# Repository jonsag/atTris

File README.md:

# atTris

## tinyTris

Adapted from work by jaromaz at [https://github.com/jaromaz/ATtiny-Tetris-Gold](https://github.com/jaromaz/ATtiny-Tetris-Gold).  

### Hardware

AS programmer I use [this one](https://github.com/jonsag/ardAVRProgrammer)  

### Software

Connect the avrProgrammer  
Insert the MCU  

Upload the hex  

>$ avrdude -c avrisp -b 19200 -p t85 -P /dev/ttyUSB0 -v -U flash:w:ATtiny-Tetris-Gold.ino.tiny8.hex:i

Set fuses  

>$ avrdude -c avrisp -b 19200 -p t85 -P /dev/ttyUSB0 -v -U lfuse:w:0xf1:m -U hfuse:w:0xdf:m -U efuse:w:0xff:m

## megaTris

My adaption of robsoncuoto's project at [https://github.com/robsoncouto/gm328a_rev_eng](https://github.com/robsoncouto/gm328a_rev_eng).  

## Notes

Reading of ATtiny85, no1, with Tetris  

    Atmega chip detector.
    Written by Nick Gammon.
    Version 1.20
    Compiled on Feb 15 2021 at 16:17:48 with Arduino IDE 10813.
    Attempting to enter ICSP programming mode ...
    Entered programming mode OK.
    Signature = 0x1E 0x93 0x0B 
    Processor = ATtiny85
    Flash memory size = 8192 bytes.
    LFuse = 0x62 
    HFuse = 0xDF 
    EFuse = 0xFF 
    Lock byte = 0xFF 
    Clock calibration = 0x91 
    No bootloader support.

    First 256 bytes of program memory:

    00: 0x4F 0xC2 0x26 0xC5 0x27 0xC9 0x67 0xC2 0x66 0xC2 0x7E 0xCA 0x64 0xC2 0x63 0xC2 
    10: 0x62 0xC2 0x61 0xC2 0x60 0xC2 0x5F 0xC2 0x5E 0xC2 0x5D 0xC2 0x5C 0xC2 0x77 0x77 
    20: 0x00 0x00 0x70 0x77 0x70 0x00 0x70 0x00 0x70 0x77 0x70 0x07 0x70 0x07 0x70 0x07 
    30: 0x00 0xEE 0x70 0x77 0x00 0x0E 0x70 0x07 0xEE 0x00 0x00 0x00 0x00 0x00 0x00 0x00 
    40: 0x00 0x00 0x00 0x00 0x00 0x3F 0x00 0x00 0x00 0x00 0x00 0x00 0x00 0x00 0x00 0x0C 
    50: 0x0C 0x00 0x60 0x30 0x18 0x0C 0x06 0x03 0x01 0x00 0x3E 0x63 0x73 0x7B 0x6F 0x67 
    60: 0x3E 0x00 0x0C 0x0E 0x0C 0x0C 0x0C 0x0C 0x3F 0x00 0x1E 0x33 0x30 0x1C 0x06 0x33 
    70: 0x3F 0x00 0x1E 0x33 0x30 0x1C 0x30 0x33 0x1E 0x00 0x38 0x3C 0x36 0x33 0x7F 0x30 
    80: 0x78 0x00 0x3F 0x03 0x1F 0x30 0x30 0x33 0x1E 0x00 0x1C 0x06 0x03 0x1F 0x33 0x33 
    90: 0x1E 0x00 0x3F 0x33 0x30 0x18 0x0C 0x0C 0x0C 0x00 0x1E 0x33 0x33 0x1E 0x33 0x33 
    A0: 0x1E 0x00 0x1E 0x33 0x33 0x3E 0x30 0x18 0x0E 0x00 0x0C 0x1E 0x33 0x33 0x3F 0x33 
    B0: 0x33 0x00 0x3F 0x66 0x66 0x3E 0x66 0x66 0x3F 0x00 0x3C 0x66 0x03 0x03 0x03 0x66 
    C0: 0x3C 0x00 0x1F 0x36 0x66 0x66 0x66 0x36 0x1F 0x00 0x7F 0x46 0x16 0x1E 0x16 0x46 
    D0: 0x7F 0x00 0x7F 0x46 0x16 0x1E 0x16 0x06 0x0F 0x00 0x3C 0x66 0x03 0x03 0x73 0x66 
    E0: 0x7C 0x00 0x33 0x33 0x33 0x3F 0x33 0x33 0x33 0x00 0x1E 0x0C 0x0C 0x0C 0x0C 0x0C 
    F0: 0x1E 0x00 0x78 0x30 0x30 0x30 0x33 0x33 0x1E 0x00 0x67 0x66 0x36 0x1E 0x36 0x66 

    Programming mode off.

Reading of ATtiny85, no2, with Tetris  

    Atmega chip detector.
    Written by Nick Gammon.
    Version 1.20
    Compiled on Feb 15 2021 at 16:17:48 with Arduino IDE 10813.
    Attempting to enter ICSP programming mode ...
    Entered programming mode OK.
    Signature = 0x1E 0x93 0x0B 
    Processor = ATtiny85
    Flash memory size = 8192 bytes.
    LFuse = 0xF1 
    HFuse = 0xDF 
    EFuse = 0xFF 
    Lock byte = 0xFF 
    Clock calibration = 0x86 
    No bootloader support.

    First 256 bytes of program memory:

    00: 0x4F 0xC2 0x26 0xC5 0x27 0xC9 0x67 0xC2 0x66 0xC2 0x7E 0xCA 0x64 0xC2 0x63 0xC2 
    10: 0x62 0xC2 0x61 0xC2 0x60 0xC2 0x5F 0xC2 0x5E 0xC2 0x5D 0xC2 0x5C 0xC2 0x77 0x77 
    20: 0x00 0x00 0x70 0x77 0x70 0x00 0x70 0x00 0x70 0x77 0x70 0x07 0x70 0x07 0x70 0x07 
    30: 0x00 0xEE 0x70 0x77 0x00 0x0E 0x70 0x07 0xEE 0x00 0x00 0x00 0x00 0x00 0x00 0x00 
    40: 0x00 0x00 0x00 0x00 0x00 0x3F 0x00 0x00 0x00 0x00 0x00 0x00 0x00 0x00 0x00 0x0C 
    50: 0x0C 0x00 0x60 0x30 0x18 0x0C 0x06 0x03 0x01 0x00 0x3E 0x63 0x73 0x7B 0x6F 0x67 
    60: 0x3E 0x00 0x0C 0x0E 0x0C 0x0C 0x0C 0x0C 0x3F 0x00 0x1E 0x33 0x30 0x1C 0x06 0x33 
    70: 0x3F 0x00 0x1E 0x33 0x30 0x1C 0x30 0x33 0x1E 0x00 0x38 0x3C 0x36 0x33 0x7F 0x30 
    80: 0x78 0x00 0x3F 0x03 0x1F 0x30 0x30 0x33 0x1E 0x00 0x1C 0x06 0x03 0x1F 0x33 0x33 
    90: 0x1E 0x00 0x3F 0x33 0x30 0x18 0x0C 0x0C 0x0C 0x00 0x1E 0x33 0x33 0x1E 0x33 0x33 
    A0: 0x1E 0x00 0x1E 0x33 0x33 0x3E 0x30 0x18 0x0E 0x00 0x0C 0x1E 0x33 0x33 0x3F 0x33 
    B0: 0x33 0x00 0x3F 0x66 0x66 0x3E 0x66 0x66 0x3F 0x00 0x3C 0x66 0x03 0x03 0x03 0x66 
    C0: 0x3C 0x00 0x1F 0x36 0x66 0x66 0x66 0x36 0x1F 0x00 0x7F 0x46 0x16 0x1E 0x16 0x46 
    D0: 0x7F 0x00 0x7F 0x46 0x16 0x1E 0x16 0x06 0x0F 0x00 0x3C 0x66 0x03 0x03 0x73 0x66 
    E0: 0x7C 0x00 0x33 0x33 0x33 0x3F 0x33 0x33 0x33 0x00 0x1E 0x0C 0x0C 0x0C 0x0C 0x0C 
    F0: 0x1E 0x00 0x78 0x30 0x30 0x30 0x33 0x33 0x1E 0x00 0x67 0x66 0x36 0x1E 0x36 0x66 

    Programming mode off.

## ATtinyArcade

[webbgoggles, AttinyArcade](https://github.com/webboggles/AttinyArcade)

## More games

[andyhighnumber, Attiny-Arduino-Games](https://github.com/andyhighnumber/Attiny-Arduino-Games)  
>>>>>>> 1e57dbd8131bc683bb3b376d9e93d66b33e94c2e

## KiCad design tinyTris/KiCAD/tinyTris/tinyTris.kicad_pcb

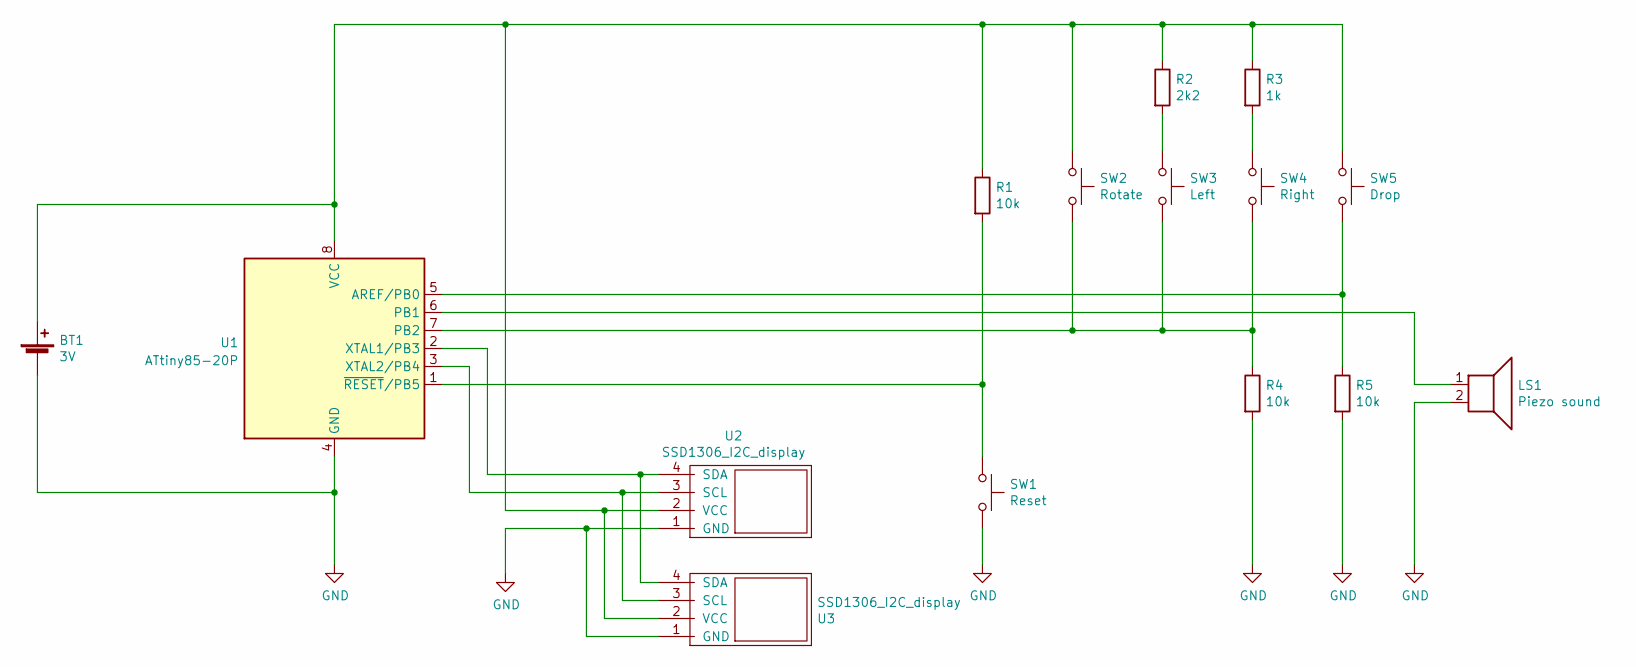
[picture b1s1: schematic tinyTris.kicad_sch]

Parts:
BT1: 3V; BatteryHolder_Keystone_103_1x20mm
LS1: Piezo sound; Buzzer_TDK_PS1240P02BT_D12.2mm_H6.5mm_large
R1, R4, R5: 10k; R_Axial_DIN0207_L6.3mm_D2.5mm_P10.16mm_Horizontal_larger_pa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
R2: 2k2; R_Axial_DIN0207_L6.3mm_D2.5mm_P10.16mm_Horizontal_larger_pa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
R3: 1k; R_Axial_DIN0207_L6.3mm_D2.5mm_P10.16mm_Horizontal_larger_pa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
SW1: Reset; SW_PUSH_6mm_large
SW2: Rotate; SW_PUSH_6mm_large
SW3: Left; SW_PUSH_6mm_large
SW4: Right; SW_PUSH_6mm_large
SW5: Drop; SW_PUSH_6mm_large
U1: ATtiny85-20P; DIP-8_W7.62mm_Socket_w_dip_packet_LongPads
U2: SSD1306_I2C_display; SSD1306_I2C_0.96_OLED_display_no_display_large
U3: SSD1306_I2C_display; SSD1306_I2C_0.96_OLED_display_large

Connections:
GND: BT1.2 (-), LS1.2, R4.2, R5.2, SW1.2, U1.4 (GND), U2.1 (GND), U3.1 (GND)
unnamed: BT1.1 (+), R1.1, R2.1, R3.1, SW2.1, SW5.1, U1.8 (VCC), U2.2 (VCC), U3.2 (VCC)
unnamed: LS1.1, U1.6 (PB1)
unnamed: R1.2, SW1.1, U1.1 (~RESET/PB5)
unnamed: R2.2, SW3.1
unnamed: R3.2, SW4.1
unnamed: R4.1, SW2.2, SW3.2, SW4.2, U1.7 (PB2)
unnamed: R5.1, SW5.2, U1.5 (AREF/PB0)
unnamed: U1.2 (XTAL1/PB3), U2.4 (SDA), U3.4 (SDA)
unnamed: U1.3 (XTAL2/PB4), U2.3 (SCL), U3.3 (SCL)

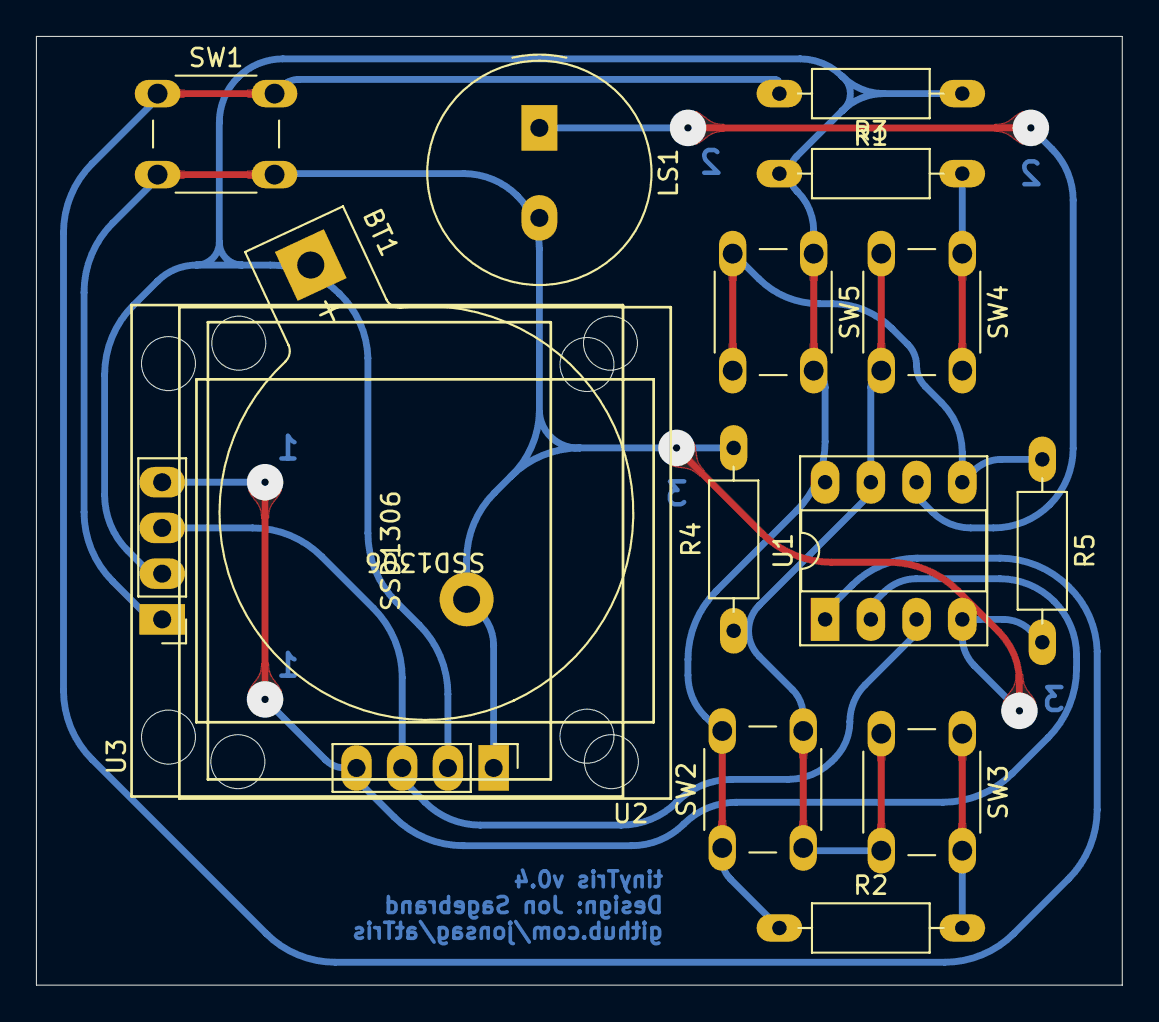
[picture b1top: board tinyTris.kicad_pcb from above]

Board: 2 copper layers, 60.3 x 52.7 mm, 15 parts (0 on the bottom side), 10 nets.

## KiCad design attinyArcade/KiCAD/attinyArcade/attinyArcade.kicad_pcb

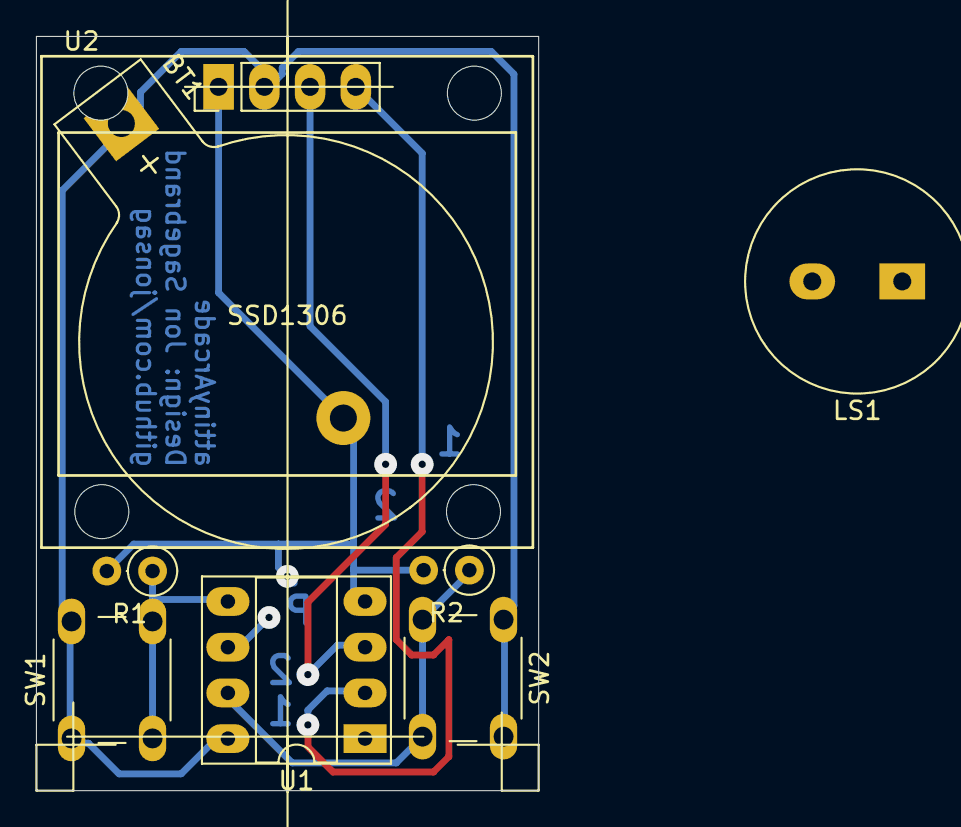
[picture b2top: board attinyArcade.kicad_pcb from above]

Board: 2 copper layers, 27.9 x 41.9 mm, 8 parts (0 on the bottom side), 7 nets.

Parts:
BT1: 3V; BatteryHolder_Keystone_103_1x20mm
LS1: Speaker; Buzzer_TDK_PS1240P02BT_D12.2mm_H6.5mm_large
R1, R2: 10k; R_Axial_DIN0207_L6.3mm_D2.5mm_P2.54mm_Vertical_large
SW1, SW2: SW_Push; SW_PUSH_6mm_large
U1: ATtiny85-20P; DIP-8_W7.62mm_Socket_w_dip_packet_LongPads
U2: SSD1306_I2C_display; SSD1306_I2C_0.96_OLED_display_large

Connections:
GND: BT1.2 (-), LS1.2, R1.2, R2.2, U1.4 (GND), U2.1 (GND)
unnamed: BT1.1 (+), SW1.1, SW2.1, U1.8 (VCC), U2.2 (VCC)
unnamed: LS1.1, U1.6 (PB1)
unnamed: R1.1, SW1.2, U1.5 (AREF/PB0)
unnamed: R2.1, SW2.2, U1.7 (PB2)
unnamed: U1.3 (XTAL2/PB4), U2.3 (SCL)
unnamed: U1.2 (XTAL1/PB3), U2.4 (SDA)

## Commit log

2021-02-19 attinyArcade
2021-02-20 README
2022-03-24 tinyTris Kicad6
2022-03-24 arcade
2022-05-13 kicad6
2022-07-08 new schematics
2022-07-09 moved sketch
2022-07-10 moving into pio
2022-07-10 many games moved to pio
2022-07-10 three more game hex
